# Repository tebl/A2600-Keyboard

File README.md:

# Atari 2600 Keyboard

After picking up an Atari 2600 Jr. a few years back, I've tried really hard to find any love for the system. The graphics really didn't do the RF cable any justice, neither did the basic noise it produced strike any of the necessary cords on a boy that grew up with the Commodore 64 as my first system. Most of it is probably that it was such a known system that you knew about it, even if you'd never even seen one of them - and - to be honest, it'd be highly unfair to compare 70s technology with that of the early 80s. So I've kept buying the cartridge and slowly found a handful of games that I've enjoyed playing around with, among them is *Star Raiders* and the *Basic Programming*. Granted, *Star Raiders* is something that is better played on the Atari 800XL instead, but *Basic Programming* is a surprisingly fun cartridge to play around with - especially on a console!

Over to the actual project. It's all about the difficulty of getting those damn cardboard overlays that is supposed to go over the Atari 2600 Keyboard controllers, which would have been doable except for one simple fact - I've tried using one of the original keyboard controllers. They feel cheap, they hurt your hands and there's no way I'm spending more money on Atari controllers (pretty much my experience with just about any Atari system, unfortunately). So I redesigned the whole thing in order to use simple 6x6 momentary tactile buttons instead - with keycap cutouts. Finally, I spent the remainder of the weekend drawing up faceplates to go with my various cartridges.

The standard faceplate have one side with the standard numeric display, which should be familiar to anyone who've been alive since at least the 80s - the reverse is a rendition of the *Star Raiders* faceplate. The *Basic Programming* faceplate is also reversible, each side showing the relevant keys used with the left and right keyboard controllers (you need two of them) - check out [archive.org](https://archive.org/details/Basic_Programming_1979_Atari_US_a) for the original manual in case your cartridge didn't come with one. I've also taken the time to design one for the Atari 2600 [synthcart](http://www.qotile.net/synth.html) as that seems like a cool project, just a shame I've got no musical abilities whatsoever.

- [1> Building the unit](#1-building-the-unit)
  - [1.1> Soldering it together](#11-soldering-it-together)
  - [1.2> Assembling the unit](#12-assembling-the-unit)
  - [1.3> Cable bits](#13-cable-bits)
  - [1.4> Testing it out](#14-testing-it-out)
- [2> Schematic](#2-schematic)
- [3> BOM](#3-bom)

# 1> Building the unit
Building the unit assumes you have at least minor experience soldering things together, recommended is at least a soldering station with adjustable temperature to get started - usually you'll want some 60/40 solder tin (if you can get that where you live). With the equipment sorted, now comes the shopping. So head on over to the [BOM](#3-bom)-section for some information on what you need, with ebay, AliExpress and similar sites you'll need to treat these as a starting search term and get what seems to match the gallery pictures.

## 1.1> Soldering it together
The construction of this unit should be straight-forward, start by soldering in the resistors in the outlines indicated on the PCB. Next, solder in the IDC socket, the gap should point inwards and will match the illustration on the board itself.

The switches you'll need to do some size-checking on, mainly because you want something that's long enough to pop through any faceplates added on the top (include the height of keycaps) with the M3 nylon hex standoffs in between - the switches I'm using are usually listed as 6x6x8mm momentary tactile switches. Push the switches into place, turn the board over and tack them into place in one corner - before soldering the other corners, it's a good idea checking that everything looks straight.

## 1.2> Assembling the unit
The faceplates can usually be reversed, so pick the side you want to use. If you bought the *M3 nylon hex kit* as suggested, you can use four of the 8mm tall standoffs on each corner of the main PCB - fix them on the bottom using M3 nuts (snip off the remaining part of the nylon screw). Place the faceplate on top, screw it into place using - well - M3 nylon screws. Use wire cutters to cut off any metal parts protruding further down than the M3 nuts, this is just to ensure that nothing messes up the surface on my desk surface.

## 1.3> Cable bits
I've previously gone into extensive detail on making up the necessary joystick cables, more specifically you can skip on over to [C64 JoyKEY](https://github.com/tebl/C64-JoyKEY/blob/main/documentation/building.md#building-the-cables) for a more detailed instructions on how to build them.

The cliff notes is that you take a *2x5 pin IDC JTAG AVR cable* (common ebay listing description), find the end that fits nicely into the keying on the board and cut off the other. Take a female IDC flat cable DB9 connector, match up pin 1 with the red stripe on the cable and squeeze really hard, preferrably with some sort of tool, until the clamp mostly locks into place. Then you just wrap the cable over, attach the separate strain relief on the connector and push that into place as well.

## 1.4> Testing it out
Well, it's an Atari 2600 so you probably haven't got all that many options other than just plugging things in and seeing whether it all works as expected. Note that you'll need one of the various cartridges that actually support the Atari 2600 Keyboard controller in the first place, but I recommend starting with *Basic Programming* and ensuring that everything works as *"expected"*.

I say *"expected"* because doing text on a console with handheld controllers isn't the most natural thing in the work, but going though the startup tutorials should be an interesting project in itself. Thankfully the complete manual is available on [archive.org](https://archive.org/details/Basic_Programming_1979_Atari_US_a), note that as it is a document written for an American console - you might experience that the cursor colours described aren't the same as the ones described. When the cursor is white, the active command will be the top row - use the shift key and it'll move around each switch in a counter-clockwise fashion.

# 2> Schematic
The supplied KiCad files should be sufficient as both a schematic and as a  starting point for ordering PCBs (basically you could just zip the contents of the export folder and upload that on a fabrication site), the schematic is also available in [PDF-format](documentation/schematic) and this is what you'll need to print and work your way through this things don't work as expected after assembly.

# 3> BOM
Most parts should be easy to get a hold of from your favourite local electronic component shop, but given that I don't have access to such shops where I live so everything was based on whatever I could get cheapest from eBay/AliExpress (free shipping, but plan on waiting 3-4 weeks for delivery). Note that with some titles, like *Basic Programming* and *synthcart* you're required to have two controllers - so plan on buying twice the amount of parts listed.

| Reference             | Item                                                              | Count | Order  |
| --------------------- | ----------------------------------------------------------------- | ----- | ------ |
| Keyboard PCB          | Fabricate using Gerber files                                      |     1 | [PCBWay](https://www.pcbway.com/project/shareproject/Atari_2600_Keyboard.html) |
| Faceplate (Standard)  | Fabricate using Gerber files                                      |    (1)| [PCBWay](https://www.pcbway.com/project/shareproject/Atari_2600_Keyboard__Standard_faceplate_.html) |
| Faceplate (Basic)     | Fabricate using Gerber files                                      |    (1)| [PCBWay](https://www.pcbway.com/project/shareproject/Atari_2600_Keyboard__Basic_faceplate_.html) |
| Faceplate (synthcart) | Fabricate using Gerber files                                      |    (1)| [PCBWay](https://www.pcbway.com/project/shareproject/Atari_2600_Keyboard__synthcart_faceplate_.html) |
| J1 *                  | 2x5 pin male IDC socket                                           |     1 | 
| R301, R302            | 4k7 (4700) ohm resistor                                           |     2 |
| SW1-SW12              | 6x6x8mm tactile momentary switch                                  |    12 |
| SW1-SW12 Keycaps      | Push-button cap for 6x6mm momentary tactile switches              |    12 |
| DB9 cable **          | Ribbon cable (9 wires), DB-9 female IDC and 2x5 pin female IDC    |     1 |
| Mounting ***          | Nylon M3 hex standoffs 8mm                                        |    (4)|
| Mounting ***          | Nylon M3x6mm nylon screws                                         |    (4)|
| Mounting ***          | M3 nylon nut                                                      |    (4)|  

*) Can use regular double row pin headers, but it is recommended to use IDC socket as it has keying.

**) You can buy the ribbon cable, DB9 female IDC connector and 2x5 pin female IDC. The easiest however is just buying something that already has the female DB9 connector attached to a ribbon cable, then just cut off the DB9 end - finally, add the 2x5 pin female IDC connector. Pictures on my [C64 JoyKEY](https://github.com/tebl/C64-JoyKEY/blob/main/documentation/building.md#building-the-cables)-repository as that uses the exact same cable.

***) The easiest way of ordering these is to just one of the M3 nylon standoff kits on ebay, AliExpress or any similar sites. That way you'll get more than what you need in various sizes for future projects as well.

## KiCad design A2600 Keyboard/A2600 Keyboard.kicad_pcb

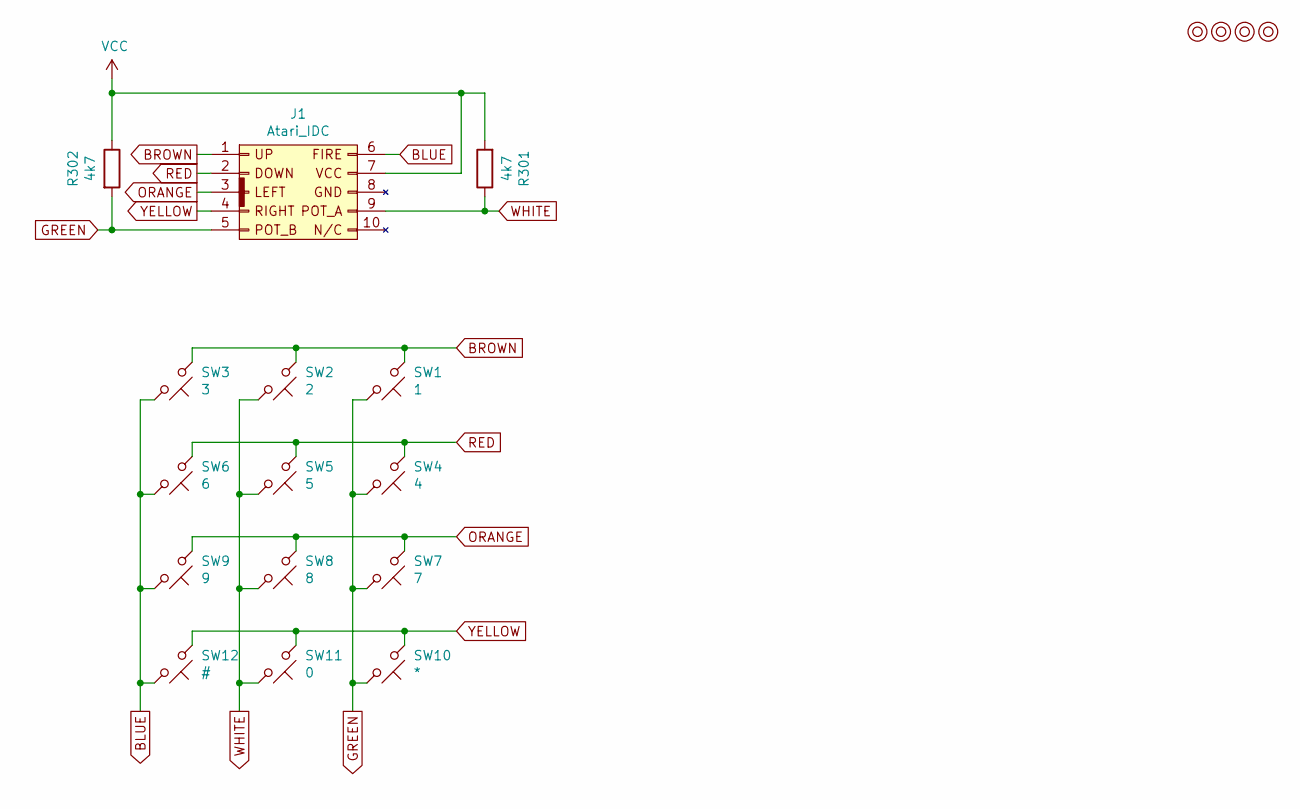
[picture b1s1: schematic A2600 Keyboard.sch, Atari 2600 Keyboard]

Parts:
J1: Atari_IDC; IDC_Joystick
M1, M2, M3, M4: Mounting; M3_pin
R301, R302: 4k7; R_Axial_DIN0207_L6.3mm_D2.5mm_P10.16mm_Horizontal
SW1: 1; SW_PUSH_6mm
SW2: 2; SW_PUSH_6mm
SW3: 3; SW_PUSH_6mm
SW4: 4; SW_PUSH_6mm
SW5: 5; SW_PUSH_6mm
SW6: 6; SW_PUSH_6mm
SW7: 7; SW_PUSH_6mm
SW8: 8; SW_PUSH_6mm
SW9: 9; SW_PUSH_6mm
SW10: *; SW_PUSH_6mm
SW11: 0; SW_PUSH_6mm
SW12: #; SW_PUSH_6mm

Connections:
BLUE: J1.6, SW3.2, SW6.2, SW9.2, SW12.2
BROWN: J1.1, SW1.1, SW2.1, SW3.1
GREEN: J1.5, R302.2, SW1.2, SW4.2, SW7.2, SW10.2
ORANGE: J1.3, SW7.1, SW8.1, SW9.1
RED: J1.2, SW4.1, SW5.1, SW6.1
VCC: J1.7, R301.2, R302.1
WHITE: J1.9, R301.1, SW2.2, SW5.2, SW8.2, SW11.2
YELLOW: J1.4, SW10.1, SW11.1, SW12.1

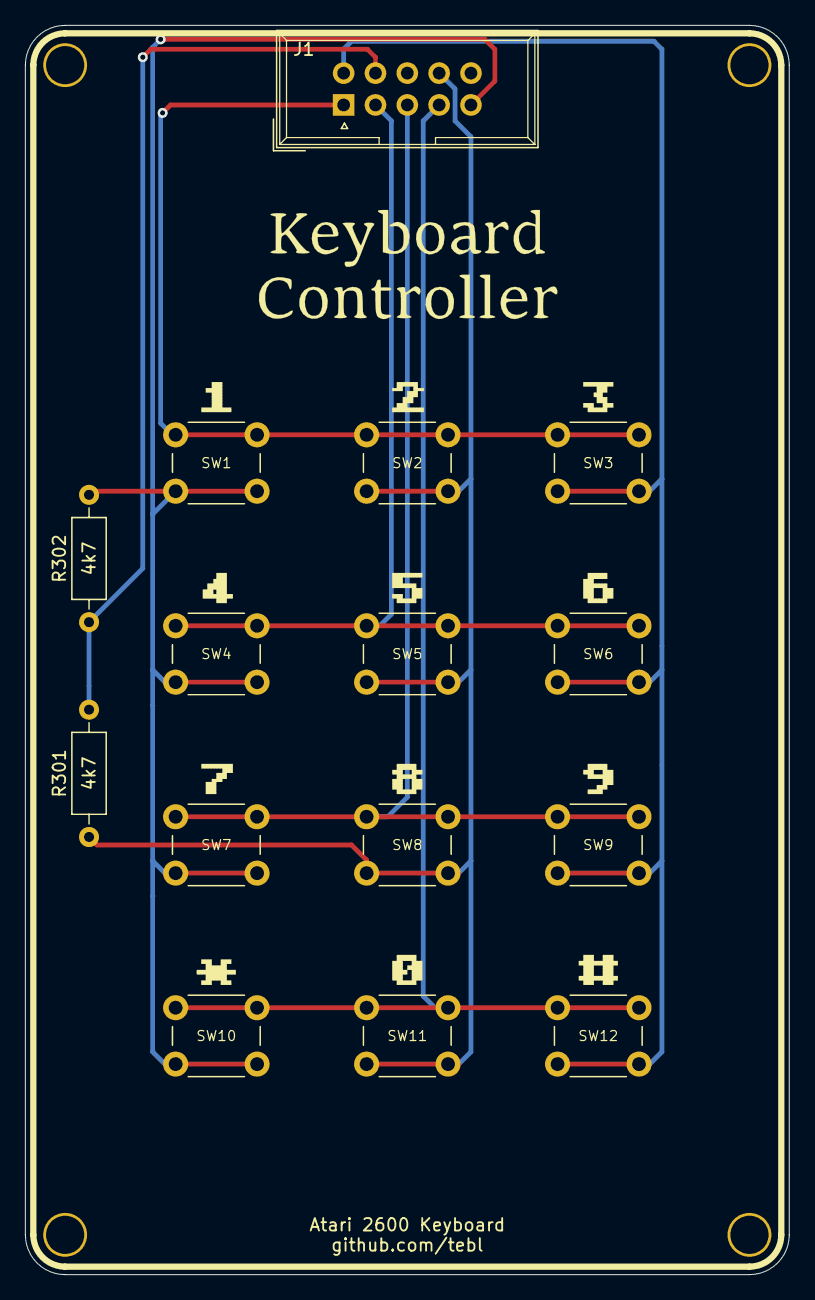
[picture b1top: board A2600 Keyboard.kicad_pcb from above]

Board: 2 copper layers, 61.0 x 99.7 mm, 19 parts (0 on the bottom side), 8 nets.

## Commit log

2021-02-21 Added schematic
2021-02-21 Layout done
2021-02-21 Gerber export and the rest of layout files
2021-02-21 Use relative library paths
2021-02-21 Plain faceplate
2021-02-21 Faceplate for BASIC
2021-02-21 Added Star Raiders
2021-02-21 Updated gerber export
2021-02-22 synthcard faceplate
2021-02-22 Making numbers great again
2021-02-23 Making keyboard numbers great again
2021-03-12 Tweaked basic faceplate and added images
2021-03-12 Larger text
2021-03-12 Updated gerber files after tweaking font sizes
2021-03-12 Changed wording
2022-04-25 Update gerber files

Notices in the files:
A2600 Keyboard/A2600 Keyboard.kicad_pcb:
Licensed under
CERN OHL v1.2
